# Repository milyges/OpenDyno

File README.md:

OpenDyno
===
Open dyno is a simple mobile car road dyno that measures power, torque, speed and other parameters in all vechicle types. It is licensed uder MIT license. OpenDyno uses UBLOX M10N GPS module to measure speed (with 4Hz sampling), so installation in car is easy and fast.

The project consists of a measurement module (board and microcontroller software written in C++ with Arduino library) and a computer application (written in C++ with QT library). Initially was developed and tested under Linux and QT6.

Project status
===
Open Dyno is currently in public alpha stage.

TODO
===

* Road tests
* Calibration
* Code clean up and optimalization

How it is look?
===

*Main window with one run loaded*

*Vechicle settings & calibration window*

*All data series visible*

*Run information detail hint*

*Example image export*

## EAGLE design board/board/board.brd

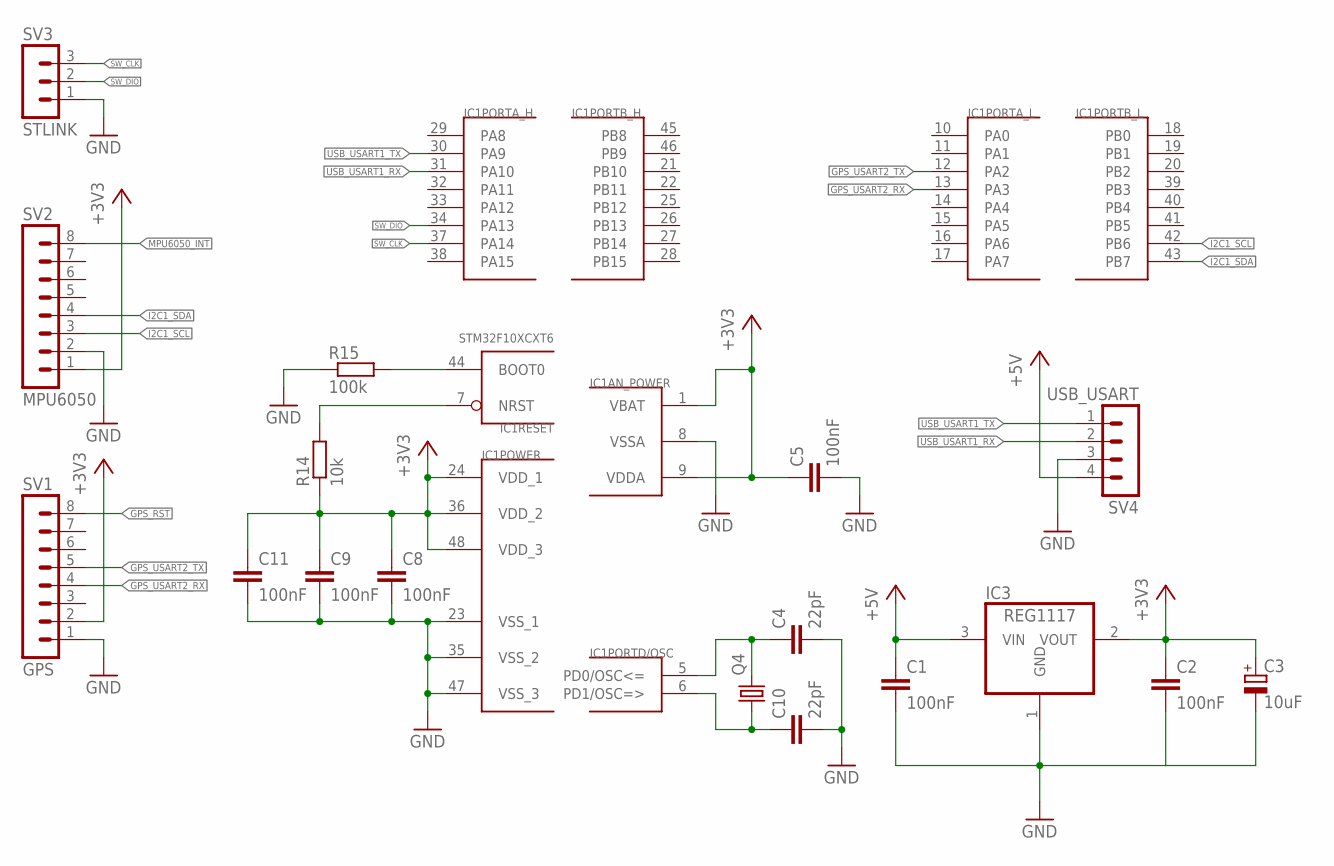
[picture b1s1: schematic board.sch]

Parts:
C1, C2, C8, C9, C11: 100nF; C0805
C3: 10uF; C/6032-28W
C4, C10: 22pF; C0805
C5: 100nF; C0603
IC1: STM32F10XCXT6; TQFP48
IC3: REG1117; SOT223
Q4: CRYSTALHC49UP; HC49UP
R14: 10k; M0805
R15: 100k; M0805
SV1: GPS; MA08-1
SV2: MPU6050; MA08-1
SV3: STLINK; MA03-1
SV4: USB_USART; MA04-1

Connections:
+3V3: C2.1, C3.+, C5.1, C8.1, C9.1, C11.1, IC1.1 (VBAT), IC1.9 (VDDA), IC1.24 (VDD_1), IC1.36 (VDD_2), IC1.48 (VDD_3), IC3.2 (VOUT), R14.1, SV1.2, SV2.1
+5V: C1.1, IC3.3 (VIN), SV4.4
GND: C1.2, C2.2, C3.-, C4.2, C5.2, C8.2, C9.2, C10.2, C11.2, IC1.8 (VSSA), IC1.23 (VSS_1), IC1.35 (VSS_2), IC1.47 (VSS_3), IC3.1 (GND), R15.1, SV1.1, SV2.2, SV3.1, SV4.3
GPS_RST: SV1.8
GPS_USART2_RX: IC1.13 (PA3), SV1.4
GPS_USART2_TX: IC1.12 (PA2), SV1.5
I2C1_SCL: IC1.42 (PB6), SV2.3
I2C1_SDA: IC1.43 (PB7), SV2.4
MPU6050_INT: SV2.8
unnamed: C4.1, IC1.5 (PD0/OSC<=), Q4.2
unnamed: IC1.7 (NRST), R14.2
unnamed: C10.1, IC1.6 (PD1/OSC=>), Q4.1
unnamed: IC1.44 (BOOT0), R15.2
SW_CLK: IC1.37 (PA14), SV3.3
SW_DIO: IC1.34 (PA13), SV3.2
USB_USART1_RX: IC1.31 (PA10), SV4.2
USB_USART1_TX: IC1.30 (PA9), SV4.1

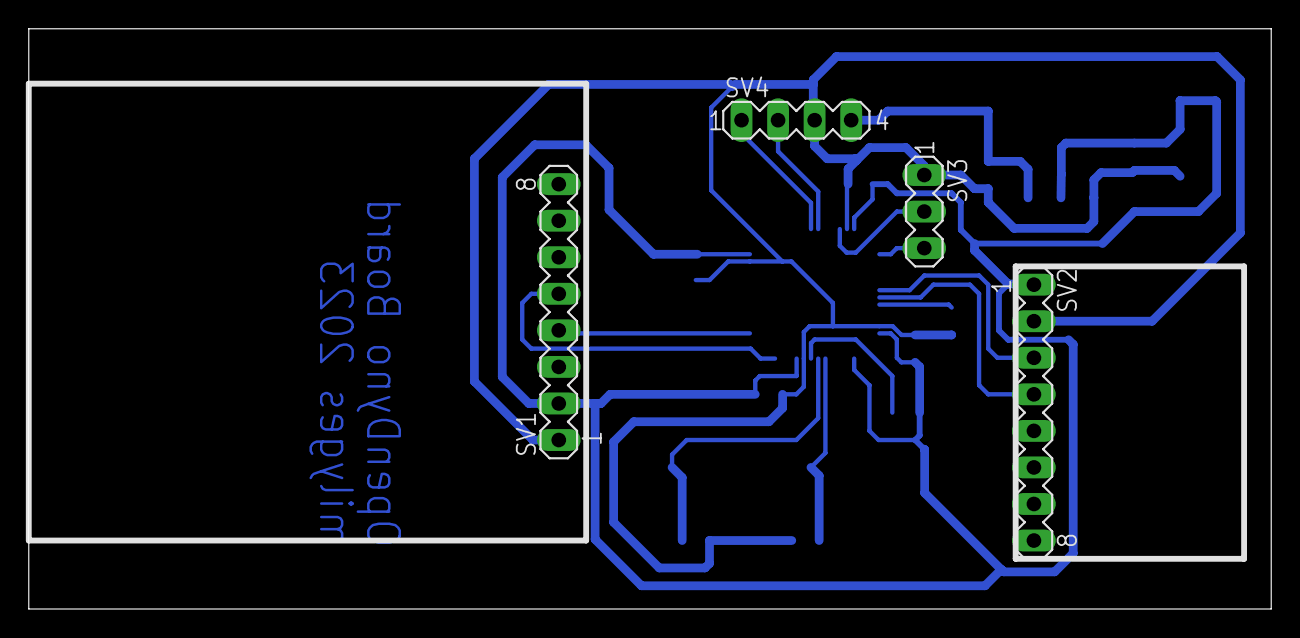
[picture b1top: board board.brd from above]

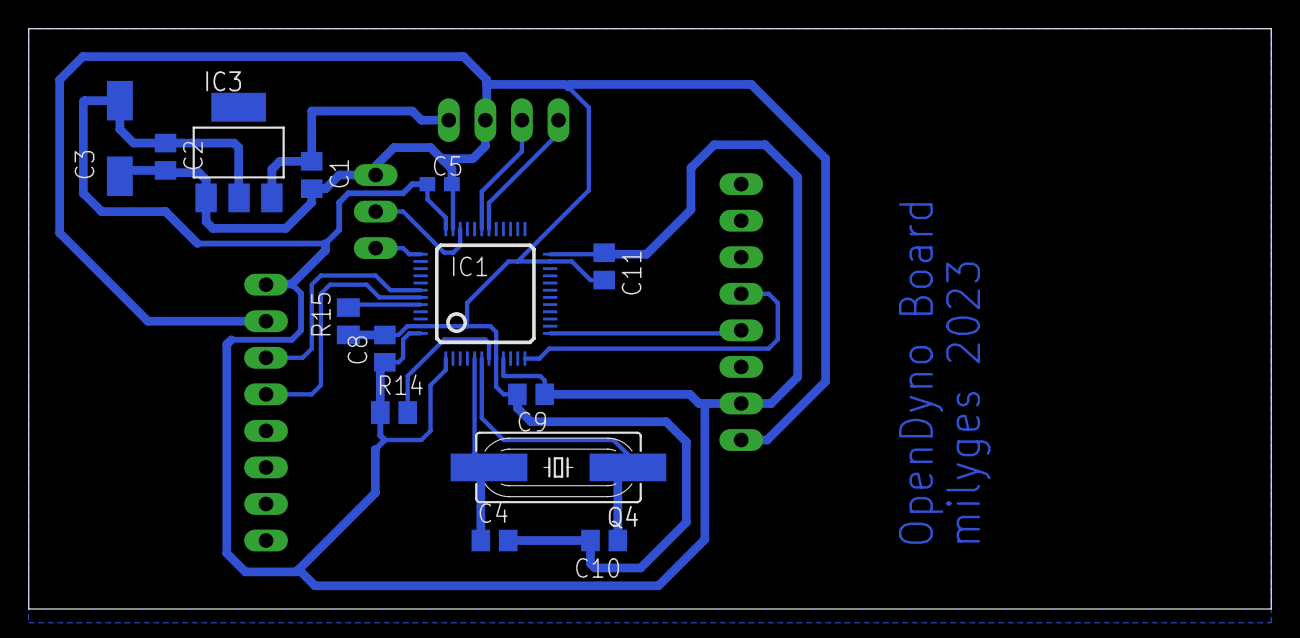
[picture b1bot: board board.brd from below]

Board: 2 copper layers, 86.3 x 40.3 mm, 18 parts (14 on the bottom side), 15 nets.

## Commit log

2024-01-07 Initial import
2024-01-07 Add screenshots
2024-01-07 Fix main window title
2024-01-07 Disable some debug messages
2024-01-09 Add license
2024-01-09 Draw optimalization & add 'demo/symulator' mode for testing
2024-02-06 Poprawki i rozwoj aplikacji
2024-02-06 Poprawki po testach drogowych
2024-02-07 Poprawki + dodanie screenshota
2024-02-07 Poprawka literówki
2024-02-08 Imlementacja informacji o użytkowniku oraz eksportu do PNG
2024-02-08 Implementacja znaku wodnego
2024-02-08 Implementacja wyświetlania wyników na wykresie
2024-02-09 Poprawki w rysowaniu oraz wstępna kablibracja
2024-02-09 Drobne poprawki/optymalizacje
2024-02-09 Dodanie konfigurowalnych filtrow i korekcji
2024-04-24 Buxfixes + count down when calculating losses
2024-04-24 Bugfixes
2024-06-09 Poprawka błędu eksportu obrazu
2024-06-14 Usunięcie filtrowania z płytki
2024-06-14 Dodanie okna z prędkością i przyśpieszeniem
2024-06-16 Poprawki filtrów po testach drogowych
2024-06-16 Dodanie screenshotow
2024-06-16 Zmiana formatów screenshotow
2024-06-16 Literowka
